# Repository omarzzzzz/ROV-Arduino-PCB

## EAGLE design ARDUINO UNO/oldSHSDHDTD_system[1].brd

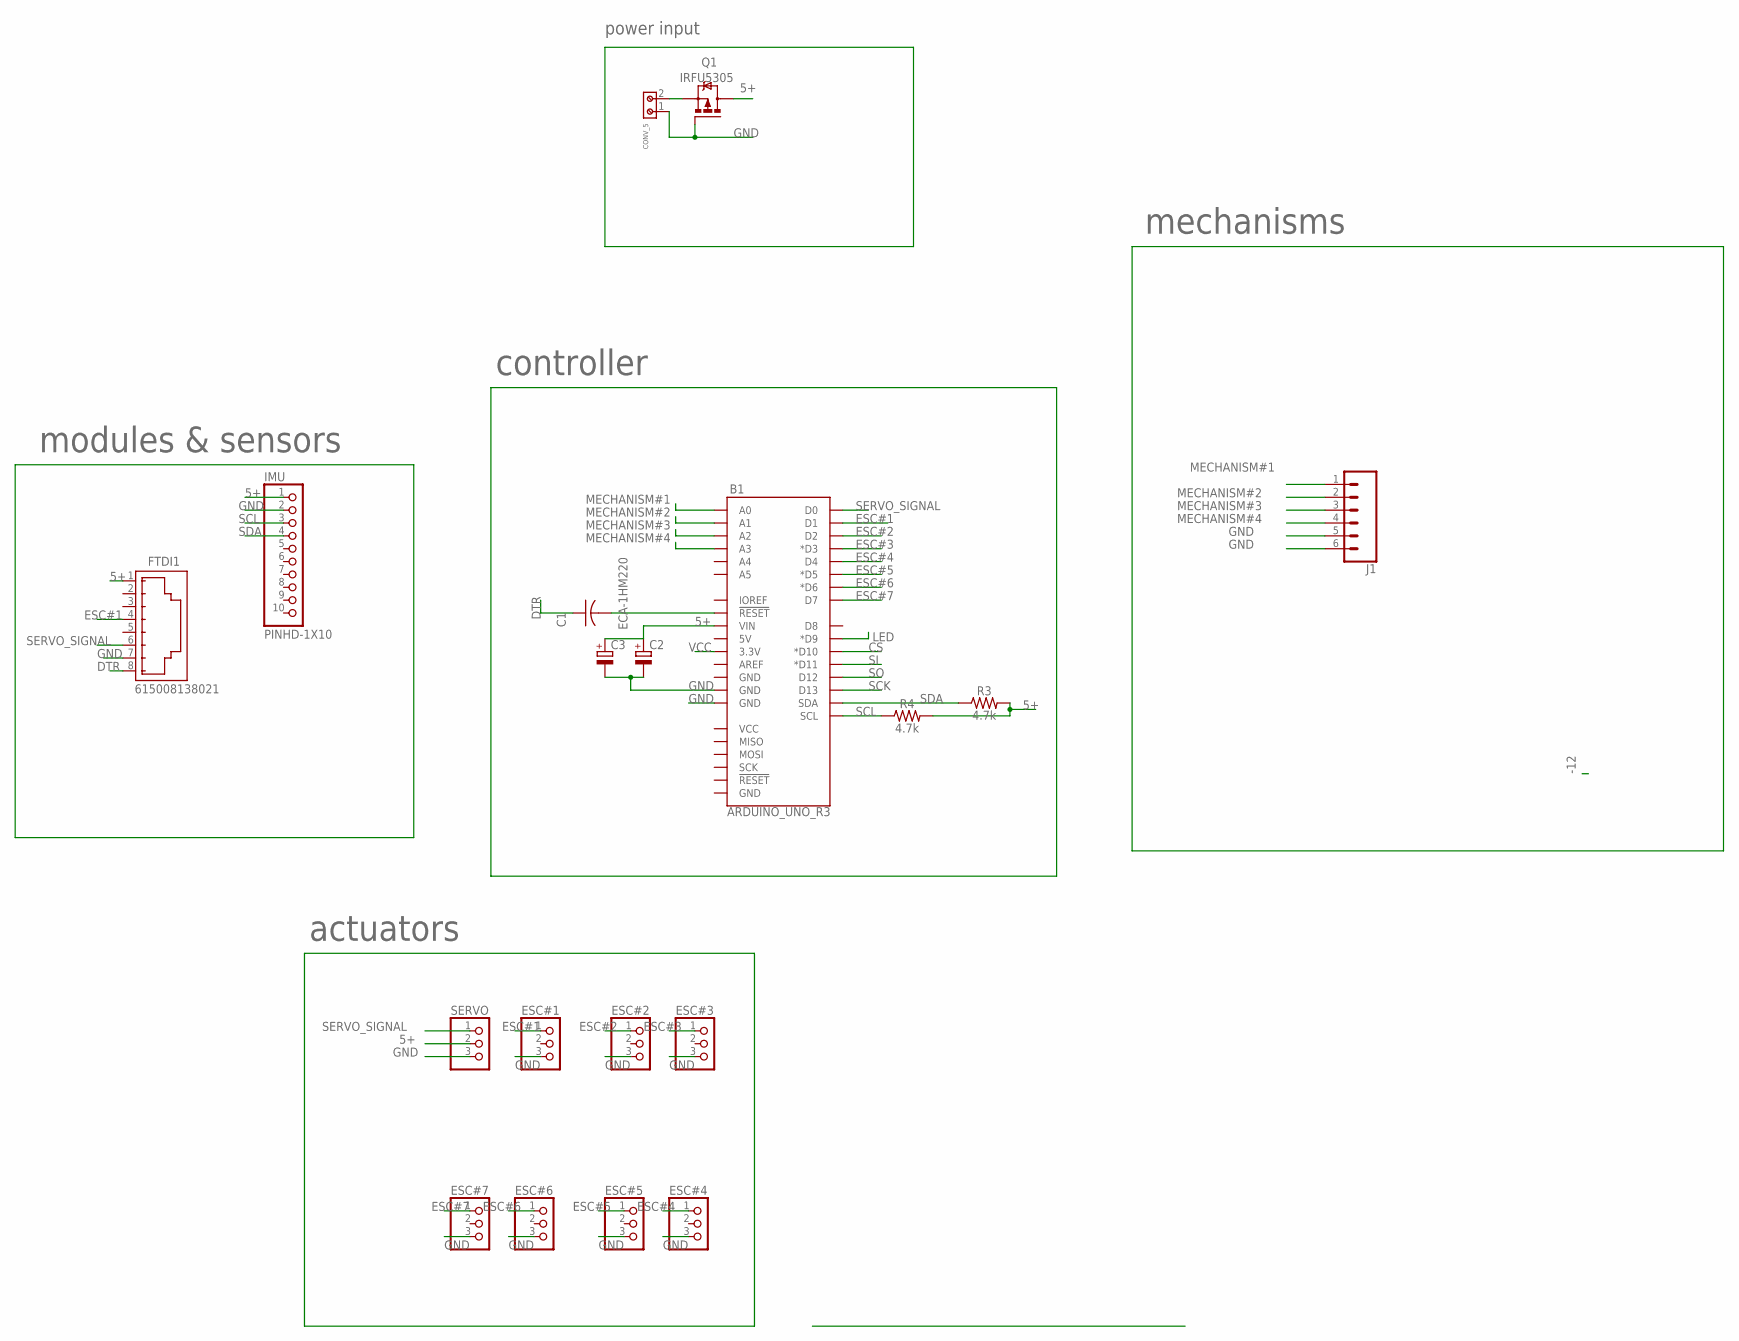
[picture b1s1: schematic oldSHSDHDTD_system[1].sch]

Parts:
B1: ARDUINO_UNO_R3; ARDUINO_R3
C1: ECA-1HM220; CAP_RADIAL_2MM
C2, C3: CPOL-EUE7.5-16; E7,5-16
CONV_5: 691213500002
ESC#1, ESC#2, ESC#3, ESC#4, ESC#5, ESC#6, ESC#7: PINHD-1X3; 1X03
FTDI1: 615008138021
IMU: PINHD-1X10; 1X10-BIG
J1: CONN_06LOCK_LONGPADS; 1X06_LOCK_LONGPADS
Q1: IRFU5305; I-PAK_TO251AA
R3, R4: 4.7k; AXIAL-0.3
SERVO: PINHD-1X3; 1X03

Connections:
5+: B1.VIN, C2.+, C3.+, FTDI1.1 (8), IMU.1, Q1.2 (D), R3.P$2 (2), R4.P$2 (2), SERVO.2
CS: B1.D10 (*D10)
DTR: C1.1, FTDI1.8 (1)
ESC#1: B1.D1, ESC#1.1, FTDI1.4 (5)
ESC#2: B1.D2, ESC#2.1
ESC#3: B1.D3 (*D3), ESC#3.1
ESC#4: B1.D4, ESC#4.1
ESC#5: B1.D5 (*D5), ESC#5.1
ESC#6: B1.D6 (*D6), ESC#6.1
ESC#7: B1.D7, ESC#7.1
GND: B1.GND@2 (GND), B1.GND@3 (GND), C2.-, C3.-, CONV_5.1, ESC#1.3, ESC#2.3, ESC#3.3, ESC#4.3, ESC#5.3, ESC#6.3, ESC#7.3, FTDI1.7 (2), IMU.2, J1.5, J1.6, Q1.1 (G), SERVO.3
LED: B1.D9 (*D9)
MECHANISM#1: B1.A0, J1.1
MECHANISM#2: B1.A1, J1.2
MECHANISM#3: B1.A2, J1.3
MECHANISM#4: B1.A3, J1.4
unnamed: B1.RESET@1 (!RESET!), C1.2
unnamed: CONV_5.2, Q1.3 (S)
SCK: B1.D13
SCL: B1.SCL, IMU.3, R4.P$1 (1)
SDA: B1.SDA, IMU.4, R3.P$1 (1)
SERVO_SIGNAL: B1.D0, FTDI1.6 (3), SERVO.1
SI: B1.D11 (*D11)
SO: B1.D12
VCC: B1.3.3V

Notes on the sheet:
mechanisms
power input
actuators
modules & sensors
controller

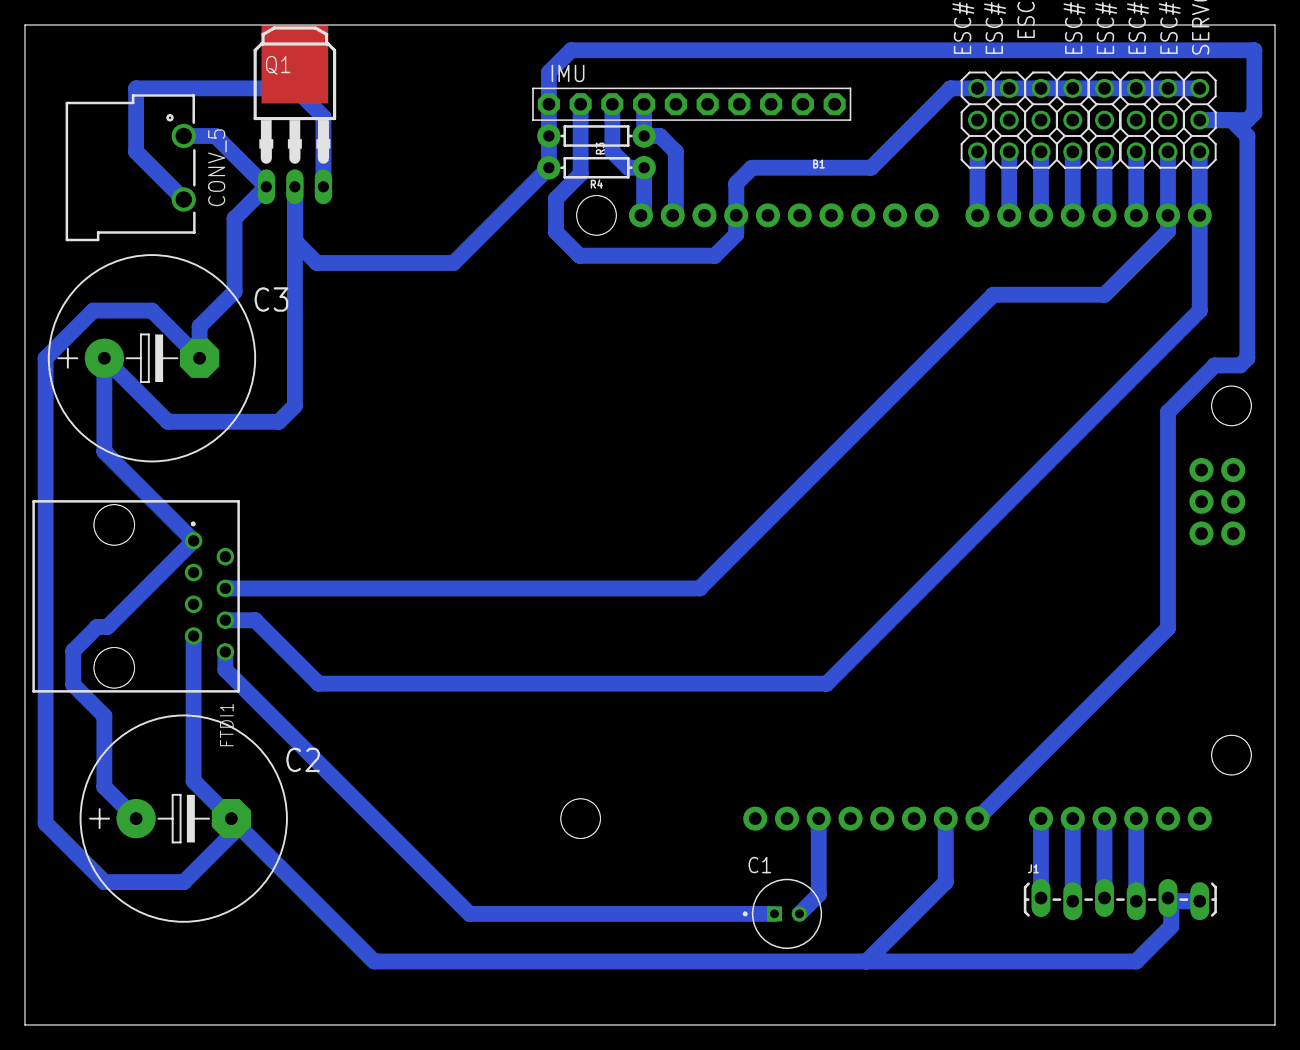
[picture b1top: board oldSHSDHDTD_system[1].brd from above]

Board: 2 copper layers, 100.0 x 80.0 mm, 19 parts (0 on the bottom side), 19 nets.

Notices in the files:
parts and their libraries:
SparkFun-Boards: Licensing: Creative Commons ShareAlike 4.0 International - https://creativecommons.org/licenses/by-sa/4.0
Wurth_Connectors_WR-TBL Rising Cage Clam: Copyright: Würth Elektronik
